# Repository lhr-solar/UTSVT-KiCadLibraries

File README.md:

# Common Libraries
This repository contains the footprint and symbol libraries that are used among us, the Longhorn Racing Solar Vehicles Team. 
In order to work on the hardware for our system, please follow the below standard practices when designing a new board.

# Using this Repository
In order to use the files in this repository, you must:
1. Add this repository as a submodule to the PCB repository. It will then show up as a folder within the PCB repository.
2. Create the PCB KiCAD Project and open it in KiCAD.
3. Click on `Preferences` -> `Manage Symbol Libraries` -> `Project Specific Libraries` and add the `.lib` files (within the submodule directory) to the path.
    
    **NOTE**: Ensure all `.lib` files are named `utsvt-name`

# Board Repositories
* All board repositories should contain this repository as a submodule.
* All board repositories should be named Team-BoardName (ex. BPS-LeaderPCB) - all board names should end in PCB
* All board repositories should have zip file of gerbers for the board
* All board repositories should contain pdf with images of board schematic and board layout (with dimensions)
* All board repositories should have `BoardName-backups/*` directory in their `.gitignore` file to ignore all backups generated.
* All board repositories should have README that contains the following information
    * Boards Purpose
    * Mouser link BOM for Board
    * List of components that take up vertical/horizontal volume outside of regular board dimensions (for mechanical purposes)
    * List of LED's on board and what information they provide

# Pull Request Template
The file PULL_REQUEST_TEMPLATE.md should be copied into the main board repository directory. This file creates a checklist of 
things the hardware engineer must complete after opening a PR. After submitting a PR, you must ensure this checklist is completed. Only after
the checklist is completed will a reviewer review your board.

    **NOTE**: After making changes to your board, it is essential that you re-request a review from the reviewers. Otherwise they will not know when
to review your design again. YOU MUST BE PROACTIVE IN YOUR WORK!

When first creating your board repository, and every time the Pull Request Template is updated, you must run the following command
`cp common/PULL_REQUEST_TEMPLATE.md .` to copy the Pull Request Template into the board repository.

# Adding Components to library
1. Add component information to Standardized Mouser Components Excel Sheet (this is so other designs can take this component into consideration if the use is applicable).
    * Be sure to include component name, mouser cart link, and footprint.
2. Open the PCB that you are working on in KiCAD (under its repository)
3. Click on `Symbol Editor`, select a `UTSVT` library to add it to, and click on `Add a New Symbol`.
4. Download component symbol and footprint (or make one yourself using symbol/footprint editor in KiCAD)
    * You may not need to download footprints/symbols for some components. Some footprints/symbols will work for multiple components if they are same package/pinout.
5. If component is large (vertically or horizontally), download 3d model for component.
6. All symbols should have the following information filled out when added:
    * Name
    * Datasheet/Mouser link
    * Footprint Association
7. If adding footprint, click on `Footprint Editor`, select a `UTSVT` folder to add it to.
8. If component takes up vertical or horizontal space (buck converters, connectors, large capacitors, etc.), follow the below steps:
    1. Download footprint and store in the submodule through your PCB repository
    2. Open KiCAD through your project file in your PCB repository. Select `Preferences` -> `Configure File Paths` -> `+` -> and add the following path `$(KIPRJMOD)/common/utsvt3d/`.
    3. Now when adding the 3D Model to the footprint, just select the footprint through the footprint library, click on 3D Models, and add the name of the step file (through one of the folders in `utsvt3d`).
9. After filling out the above information, enter the submodule directory through your PCB repository.
10. There will be changes made to this submodule if everything was done correctly. Now you must commit your changes to a new branch and open a Pull Request.
11. After the Pull Request is merged, update the submodule in your PCB repository through `git submodule update`.

# Standard Constraints for Laying out Board
When manufacturing a PCB, there are constraints that are given to us by the manufacturer based on how precise their manufacturing equipment is. The following are [**JLCPCB Manufacturing Capabilities**](https://jlcpcb.com/capabilities/Capabilities).  
When creating the layout of your board, select
`File` -> `Board Setup` -> `Constraints` and set them to the following values:
* Minimum Clearance (2 layer): .127mm
* Minimum Track Width (2 layer): .127mm
* Minimum Clearance (4 layer): .09mm
* Minimum Track Width (4 layer): .09mm
* Minimum Connection Width: 0mm
* Minimum Annular Width: .13mm
* Minimum Via Diameter (2 layer): .5mm
* Minimum Via Diameter (4 layer): .25mm
* Copper to Hole Clearance: .254mm
* Copper to Edge Clearance: .3mm
* Minimum Through Hole: .3mm
* Hole to Hole Clearance: .5mm
* Minimum Item Clearance: .15mm
* Minimum Text Height: 1mm
* Minimum Text Thickness: .153mm  

Also go `File` -> `Board Setup` -> `Solder Mask/Paste` and set them to the following values:
* Solder mask expansion: .038mm
* Solder mask minimum web width: .1mm  

# Exporting a Board as a 3D Model
Before exporting a board go into the 3D viewer of KiCAD `View` -> `3D Viewer` while in the PCB editor to see what you will be exporting. 
* For mechanical integration, mechanical doesn't need to see every individual component.  If your board doesn't have any smd parts that take up vertical or horizontal space then while in the 3D viewer do `Preferences` -> `Toggle SMD 3D Models` the same applies for any tht component except it's `Preferences` -> `Toggle Through Hole 3D Models`.  
* Go to `File` -> `Export` -> `Step` and select the directory you want to export to and in the `Coordinantes` section make sure `Board Center Origin` is selected.
* Press `Export`.

# Working on a Board
* The first page of the KiCAD schematic should have a version control description of the board that is being worked on. It should list the changes between each version of the board and changes that should be made in future versions of the board.
* When working on a board, the branch name should be the version of the board.
* Versions are updated every time the layout of the board is changed after a fabrication.
* Everyone working on boards should download the Interactive HTML BOM plugin for KiCAD. After laying out the board, an interactive BOM should be generated so soldering the board is easily managed.

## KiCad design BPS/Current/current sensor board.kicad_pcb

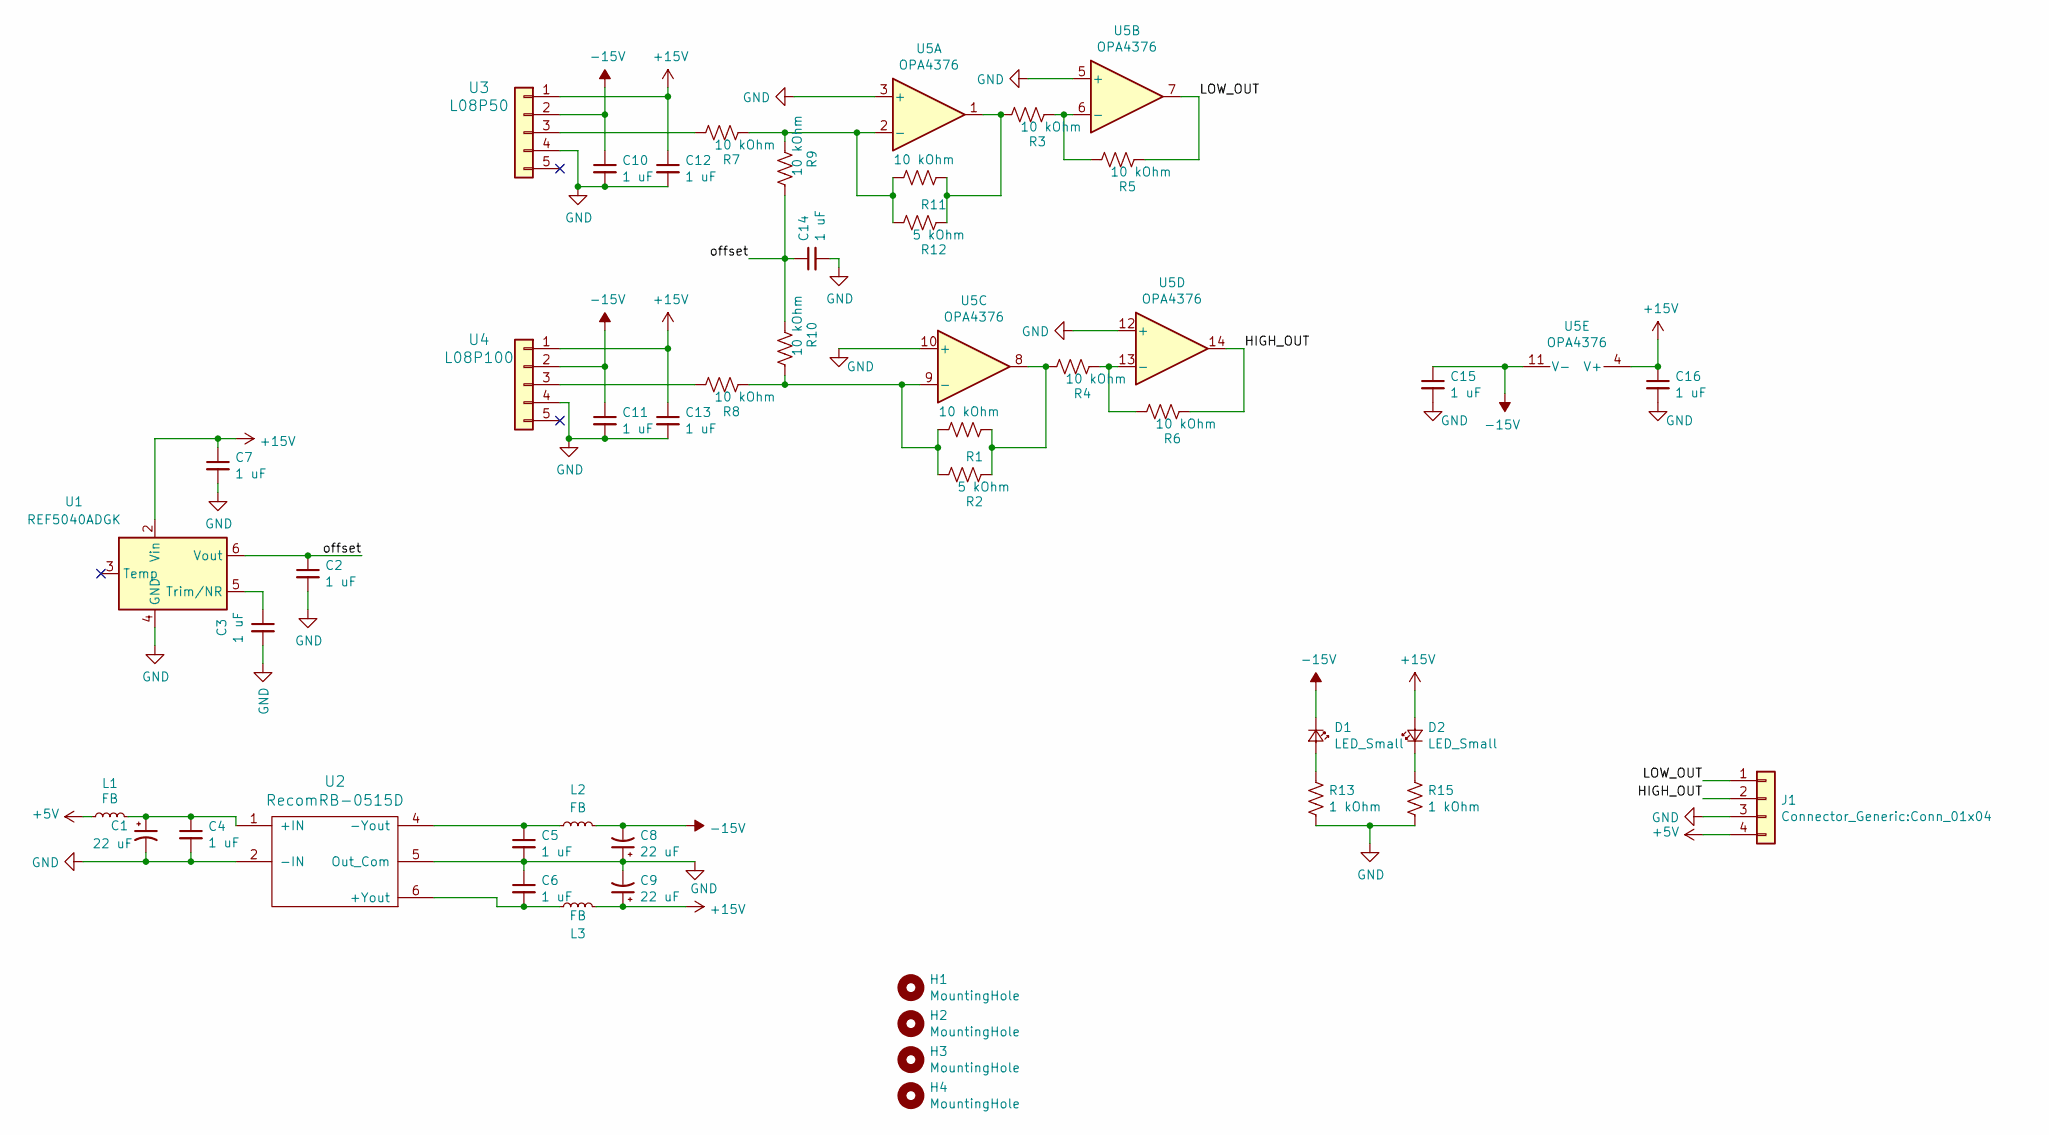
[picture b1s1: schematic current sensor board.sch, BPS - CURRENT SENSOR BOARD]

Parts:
C1, C8, C9: 22 uF; C_0805_2012Metric
C2, C3, C4, C5, C6, C7, C10, C11, C12, C13, C14, C15, C16: 1 uF; C_0805_2012Metric
D1, D2: LED_Small; LED_0805_2012Metric
H1, H2, H3, H4: MountingHole; MountingHole_3mm
J1: Connector_Generic:Conn_01x04; Molex_Micro-Fit_3.0_43650-0415_1x04_P3.00mm_Vertical
L1, L2, L3: FB; L_1206_3216Metric
R1, R3, R4, R5, R6, R7, R8, R9, R10, R11: 10 kOhm; R_0805_2012Metric
R2, R12: 5 kOhm; R_0805_2012Metric
R13, R15: 1 kOhm; R_0805_2012Metric
U1: REF5040ADGK; MSOP-8_3x3mm_P0.65mm
U2: RecomRB-0515D; SIP-7_19.6x6mm_P2.54mm
U3: L08P50; L08PxxxD15
U4: L08P100; L08PxxxD15
U5: OPA4376; TSSOP-14_4.4x5mm_P0.65mm

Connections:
+5V: J1.4, L1.1
+15V: C7.1, C9.1, C12.1, C13.1, C16.1, D2.2 (A), L3.2, U1.2 (Vin), U3.1, U4.1, U5.4 (V+)
-15V: C8.2, C10.1, C11.1, C15.1, D1.1 (K), L2.2, U3.2, U4.2, U5.11 (V-)
/HIGH_OUT: J1.2, R6.1, U5.14
/LOW_OUT: J1.1, R5.1, U5.7
/offset: C2.1, C14.1, R9.2, R10.1, U1.6 (Vout)
GND: C1.2, C2.2, C3.2, C4.2, C5.2, C6.1, C7.2, C8.1, C9.2, C10.2, C11.2, C12.2, C13.2, C14.2, C15.2, C16.2, J1.3, R13.2, R15.2, U1.4 (GND), U2.2 (-IN), U2.5 (Out_Com), U3.4, U4.4, U5.3 (+), U5.5 (+), U5.10 (+), U5.12 (+)
unnamed: C1.1, C4.1, L1.2, U2.1 (+IN)
unnamed: C3.1, U1.5 (Trim/NR)
unnamed: C5.1, L2.1, U2.4 (-Yout)
unnamed: C6.2, L3.1, U2.6 (+Yout)
unnamed: D1.2 (A), R13.1
unnamed: D2.1 (K), R15.1
unnamed: R1.1, R2.1, R4.2, U5.8
unnamed: R1.2, R2.2, R8.1, R10.2, U5.9 (-)
unnamed: R3.1, R5.2, U5.6 (-)
unnamed: R4.1, R6.2, U5.13 (-)
unnamed: R7.2, U3.3
unnamed: R8.2, U4.3
unnamed: R3.2, R11.1, R12.1, U5.1
unnamed: R7.1, R9.1, R11.2, R12.2, U5.2 (-)

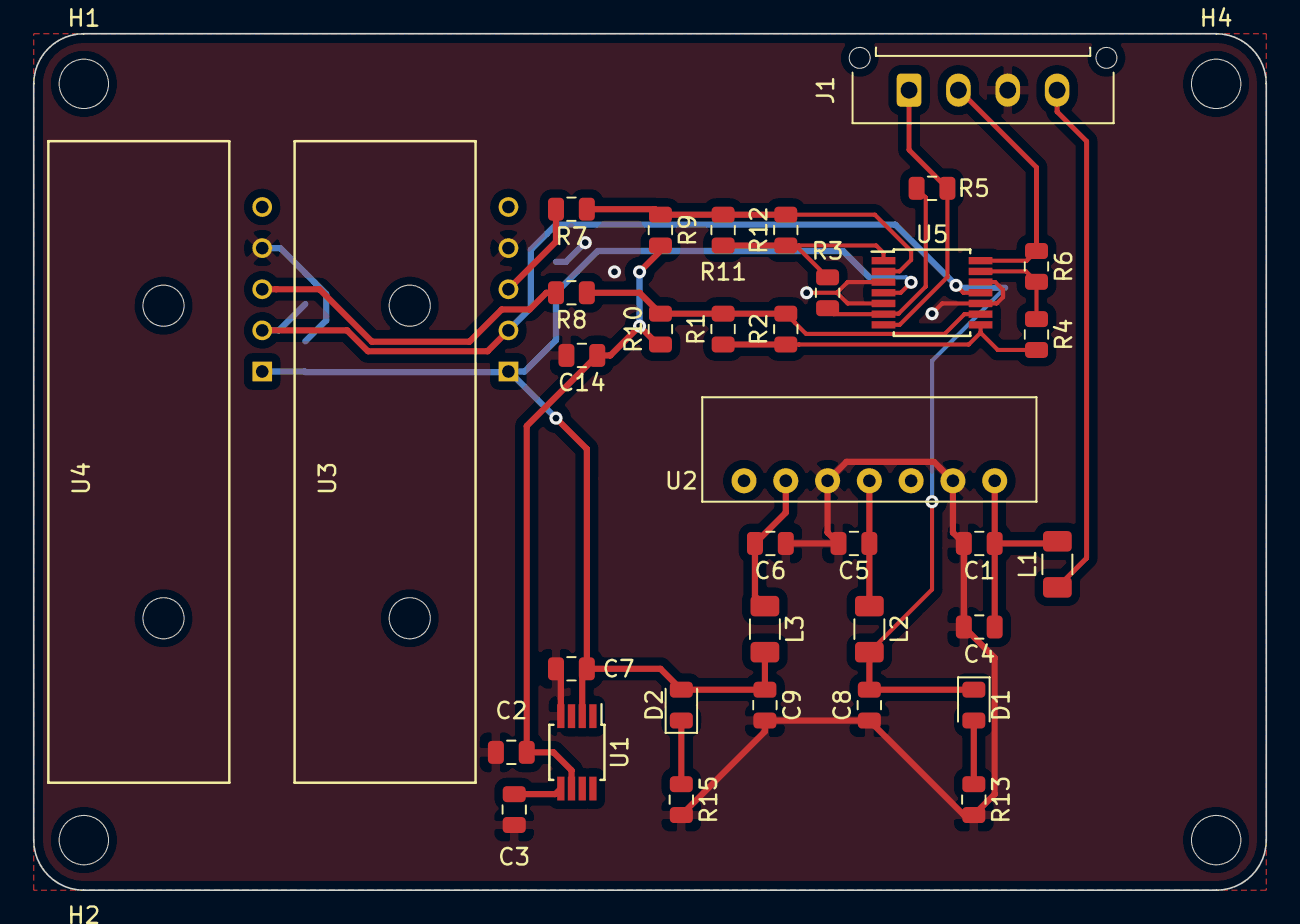
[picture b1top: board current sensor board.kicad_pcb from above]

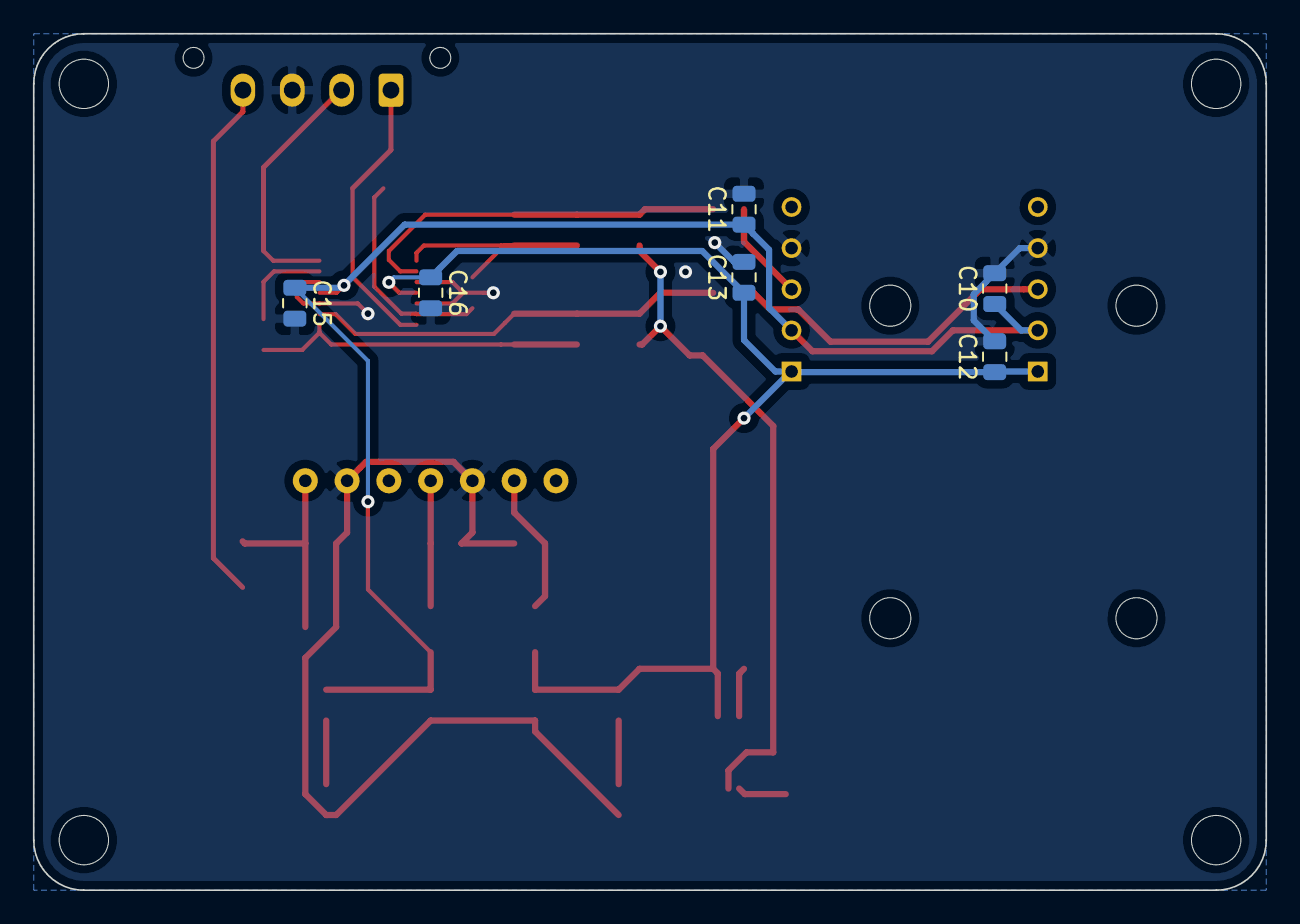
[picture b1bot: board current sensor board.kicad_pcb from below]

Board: 2 copper layers, 74.9 x 52.1 mm, 45 parts (6 on the bottom side), 21 nets.

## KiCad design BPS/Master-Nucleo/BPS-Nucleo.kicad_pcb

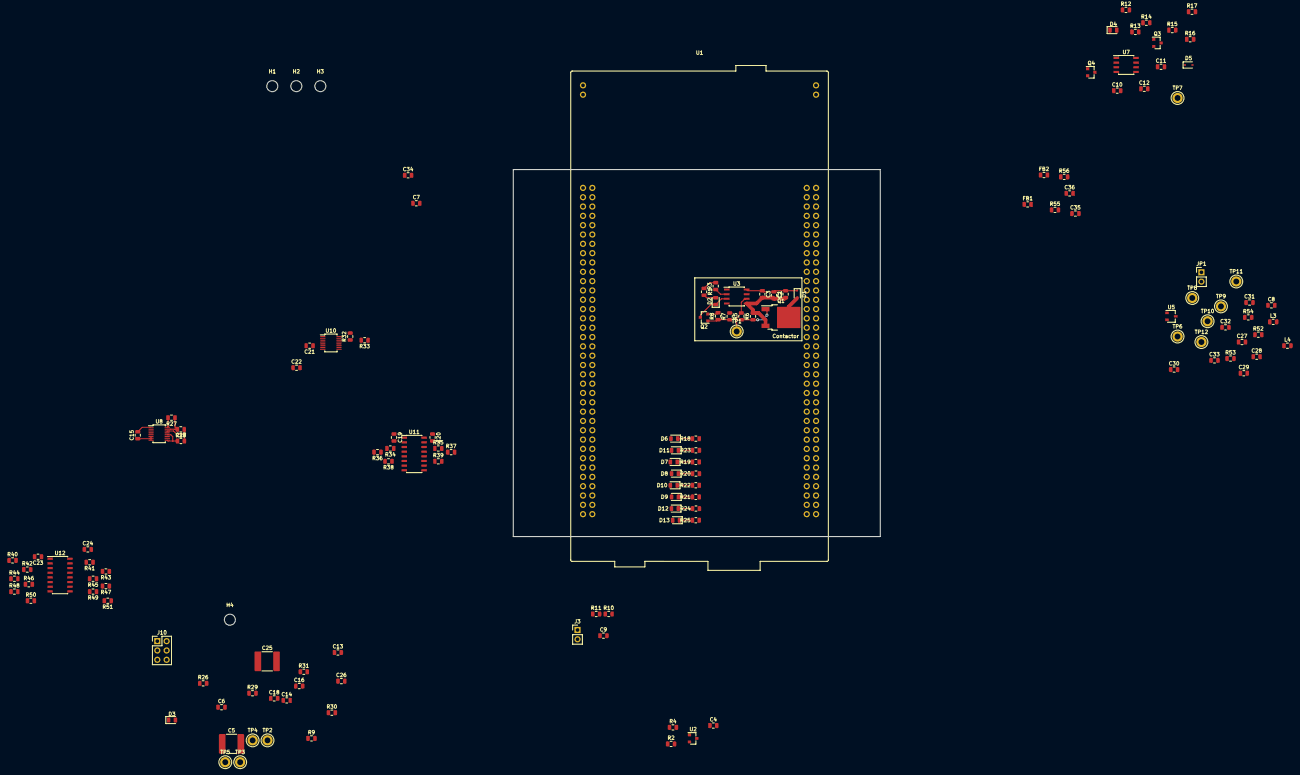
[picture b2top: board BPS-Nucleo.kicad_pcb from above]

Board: 2 copper layers, 100.0 x 100.0 mm, 141 parts (0 on the bottom side), 97 nets.

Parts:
C1, C4, C10: 1uF; C_0805_2012Metric
C2, C11, C27, C30: 10uF; C_0805_2012Metric
C3, C7, C9, C12, C15, C17, C19, C20, C21, C22, C23, C24, C28, C31, C32, C34: 0.1uF; C_0805_2012Metric
C5, C25: 470pF; C_2220_5650Metric
C6, C26: 4.7uF; C_0805_2012Metric
C8: 0.22uF; C_0805_2012Metric
C13, C14, C16, C18, C29, C33: 0.01uF; C_0805_2012Metric
C35, C36: 1u; C_0805_2012Metric
D1, D5: 1N4148WS; D_SOD-323
D2: ContactorEn; LED_0805_2012Metric
D3: PowerOn; LED_0805_2012Metric
D4: Fault; LED_0805_2012Metric
D6: Heartbeat; LED_0805_2012Metric
D7: UVolt; LED_0805_2012Metric
D8: OVolt; LED_0805_2012Metric
D9: OTemp; LED_0805_2012Metric
D10: OCurr; LED_0805_2012Metric
D11: WDError; LED_0805_2012Metric
D12: CANError; LED_0805_2012Metric
D13: Extra; LED_0805_2012Metric
FB1, FB2: 600; L_0805_2012Metric
H1, H2, H3, H4: MountingHole; MountingHole_3mm
J3: Conn_01x03; PinHeader_1x02_P2.54mm_Vertical
J10: DisplayJumper; PinHeader_2x03_P2.54mm_Vertical
JP1: Termination Resistors; PinHeader_1x02_P2.54mm_Vertical
L3, L4: 2kH; L_0805_2012Metric
Q1: VND5N07-E; TO-252-2
Q2, Q3, Q4: NTR4003NT1G; SOT-23
R1, R9: 1.5k; R_0805_2012Metric
R2, R10, R11: 4.7k; R_0805_2012Metric
R3, R12: 470; R_0805_2012Metric
R4: 1k; R_0805_2012Metric
R5, R7, R14, R16, R54: 0; R_0805_2012Metric
R6, R8, R15, R17: 10k; R_0805_2012Metric
R13: 1.6k; R_0805_2012Metric
R18: 680; R_0805_2012Metric
R19, R20, R21, R22, R23, R24, R25: 750; R_0805_2012Metric
R26: 120; R_0805_2012Metric
R27, R32: 806; R_0805_2012Metric
R28, R33: 1.21k; R_0805_2012Metric
R29, R30, R31: 49.9; R_0805_2012Metric
R34, R35, R36, R37, R38, R39, R40, R41, R42, R43, R44, R45, R46, R47, R48, R49, R50, R51: 50; R_0805_2012Metric
R52, R53: 60; R_0805_2012Metric
R55, R56: 220k; R_0805_2012Metric
TP1: ContactorGate_TP; TestPoint_Keystone_5005-5009_Compact
TP2: +12V_TP; TestPoint_Keystone_5005-5009_Compact
TP3: +5V_TP; TestPoint_Keystone_5005-5009_Compact
TP4: GNDPWR_TP; TestPoint_Keystone_5005-5009_Compact
TP5: GND_TP; TestPoint_Keystone_5005-5009_Compact
TP6: CAN_ISO_Vout; TestPoint_Keystone_5005-5009_Compact
TP7: StrobeLightGate_TP; TestPoint_Keystone_5005-5009_Compact
TP8: CAN_ISO_Vin; TestPoint_Keystone_5005-5009_Compact
TP9: CAN_ISO_GndIn; TestPoint_Keystone_5005-5009_Compact
TP10: CAN_ISO_GndOut; TestPoint_Keystone_5005-5009_Compact
TP11: CAN_H; TestPoint_Keystone_5005-5009_Compact
TP12: CAN_L; TestPoint_Keystone_5005-5009_Compact
U1: NUCLEO144-F412ZG; ST_Morpho_Connector_144_STLink
U2: BAS70-04; SOT-23
U3, U7: SI8261ABC-IS; SOIC-8_3.9x4.9mm_P1.27mm
U5: CDSOT23-T24CAN; SOT-23W
U8, U10: LTC6820; MSOP-16_3x4mm_P0.5mm
U11: Si8641EC-B-IS1; SOIC-16_3.9x9.9mm_P1.27mm
U12: SI8660EC-B-IS1; SOIC-16_3.9x9.9mm_P1.27mm

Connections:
+3V3: C7.2, C9.1, C21.1, C32.1, C33.1, J10.1, J10.2, R10.1, R11.1, U1.16, U10.6
+5V: C5.2, C15.1, C17.1, C19.1, C22.1, C23.1, C30.1, C31.1, C34.1, D4.2, R1.1, R2.2, R3.2, R9.1, R12.2, TP3.1, U1.6, U2.2, U8.6, U8.7, U8.8, U8.9, U8.12, U10.9, U10.12, U11.1, U11.7, U12.1
+5VL: C20.1, C24.1, C25.2, U11.10, U11.16, U12.16
+12V: C1.2, C2.1, C3.1, C6.1, C10.2, C11.1, C12.1, C26.1, D1.1, D5.1, TP2.1, U3.8, U7.8
/ADC1_CH2: C36.2, R56.2, U1.107
/ADC1_CH3: C35.2, R55.2, U1.109
/CAN/CAN_H: R52.2, TP11.1, U5.1
/CAN/CAN_L: R53.2, TP12.1, U5.2
/CAN/TERM_H: JP1.2, R52.1
/CAN/TERM_L: JP1.1, R53.1
/Contactor Driver/CONTACTOR_V-: D1.2, Q1.2
/DISPLAY_CS: U1.21, U10.5
/FAULT: R16.2, U1.88
/I2C3_SCL: J3.1, R10.2, U1.95
/I2C3_SDA: J3.2, R11.2, U1.73
/LTC6811_CS: U1.89, U8.5
/PA5: D13.2, U1.83
/PA6: D12.2, U1.85
/PA7: D11.2, U1.87
/PB0: R7.2, U1.34
/PB1: C4.1, R4.1, U1.96, U2.3
/PC0: D10.2, U1.38
/PC1: D9.2, U1.36
/PC2: D8.2, U1.35
/PC3: D7.2, U1.37
/RUN: D6.2, U1.28
/SPI1_CLK: R34.2, U1.103, U8.4, U10.4
/SPI1_MISO: R38.2, U1.99, U8.3, U10.3
/SPI1_MOSI: R36.2, U1.101, U8.2, U10.2
/SPI/DISP_IM: R31.1, U10.10
/SPI/DISP_IP: R30.1, U10.11
/SPI/DISP_PHA: J10.4, U10.8
/SPI/DISP_POL: J10.3, U10.7
/SPI/VOLT_IM: R26.1, R29.1, U8.10
/SPI/VOLT_IP: R26.2, U8.11
/TEMP_CS1: R40.1, U1.102
/TEMP_CS2: R42.1, U1.100
/TEMP_CS3: R44.1, U1.98
/TEMP_CS4: R46.1, U1.76
/TEMP_CS5: R48.1, U1.91
/TEMP_CS6: R50.1, U1.74
GND: C4.2, C7.1, C9.2, C13.2, C14.2, C15.2, C16.2, C17.2, C18.2, C19.2, C21.2, C22.2, C23.2, C30.2, C31.2, C32.2, C33.2, C34.2, C35.1, C36.1, D3.1, J10.5, J10.6, Q2.2, Q4.2, R8.2, R17.2, R18.2, R19.2, R20.2, R21.2, R22.2, R23.2, R24.2, R25.2, R28.1, R33.1, TP5.1, U1.8, U1.19, U1.20, U1.22, U1.49, U1.60, U1.71, U1.72, U1.81, U1.92, U1.104, U1.111, U1.126, U1.135, U1.143, U1.144, U2.1, U8.1, U8.13, U8.14, U10.1, U10.13, U10.14, U11.2, U11.8, U12.8
GNDPWR: C1.1, C2.2, C3.2, C6.2, C10.1, C11.2, C12.2, C26.2, Q1.3, Q3.2, R6.2, R15.2, TP4.1, U3.5, U7.5
GND_A: C20.2, C24.2, U11.9, U11.15, U12.9
unnamed: C8.1, L3.2, TP6.1
unnamed: C8.2, L4.2, TP10.1
unnamed: C14.1, R29.2
unnamed: C18.1, R30.2, R31.2
unnamed: C27.1, C28.1, C29.1, L3.1, TP8.1
unnamed: C27.2, C28.2, C29.2, L4.1, R54.2, TP9.1, U5.3
unnamed: D2.1, Q2.3, U3.3
unnamed: D2.2, R1.2
unnamed: D3.2, R9.2
unnamed: D4.1, R13.1
unnamed: D5.2, Q3.3
unnamed: D6.1, R18.1
unnamed: D7.1, R19.1
unnamed: D8.1, R20.1
unnamed: D9.1, R21.1
unnamed: D10.1, R22.1
unnamed: D11.1, R23.1
unnamed: D12.1, R24.1
unnamed: D13.1, R25.1
unnamed: FB1.2, R55.1
unnamed: FB2.2, R56.1
unnamed: R2.1, R4.2
unnamed: Q1.1, R5.1, R6.1
unnamed: Q2.1, R7.1, R8.1
unnamed: Q3.1, R14.1, R15.1
unnamed: Q4.1, R16.1, R17.1
unnamed: Q4.3, R13.2, U7.3
unnamed: R3.1, U3.2
unnamed: R5.2, TP1.1, U3.6
unnamed: R12.1, U7.2
unnamed: R14.2, TP7.1, U7.6
unnamed: R27.1, R28.2, U8.15
unnamed: R27.2, U8.16
unnamed: R32.1, R33.2, U10.15
unnamed: R32.2, U10.16
unnamed: R34.1, U11.3
unnamed: R35.1, U11.14
unnamed: R36.1, U11.4
unnamed: R37.1, U11.13
unnamed: R38.1, U11.6
unnamed: R39.1, U11.11
unnamed: R40.2, U12.2
unnamed: R41.2, U12.15
unnamed: R42.2, U12.3
unnamed: R43.2, U12.14
unnamed: R44.2, U12.4
unnamed: R45.2, U12.13
unnamed: R46.2, U12.5
unnamed: R47.2, U12.12
unnamed: R48.2, U12.6
unnamed: R49.2, U12.11
unnamed: R50.2, U12.7
unnamed: R51.2, U12.10

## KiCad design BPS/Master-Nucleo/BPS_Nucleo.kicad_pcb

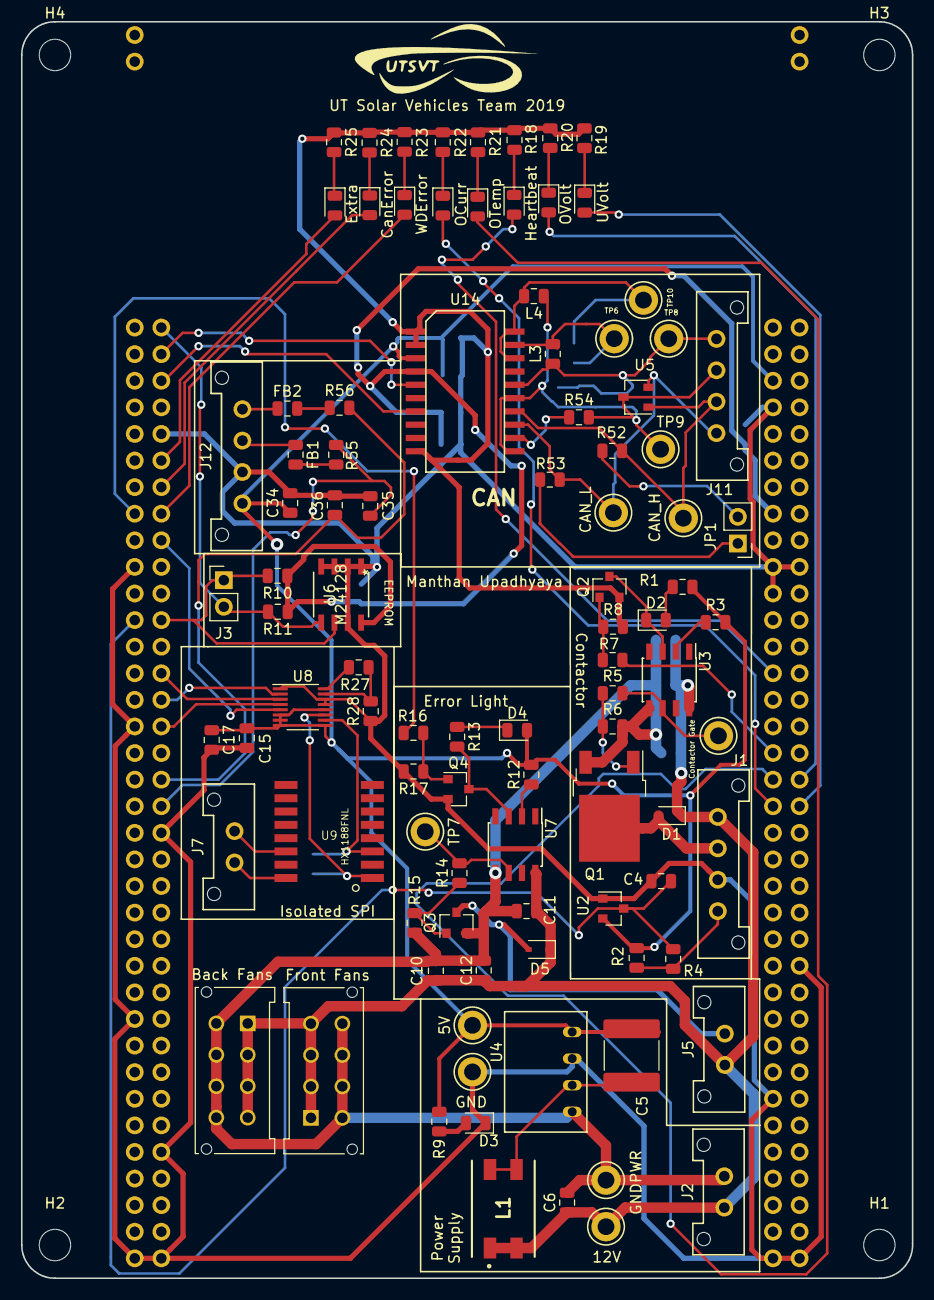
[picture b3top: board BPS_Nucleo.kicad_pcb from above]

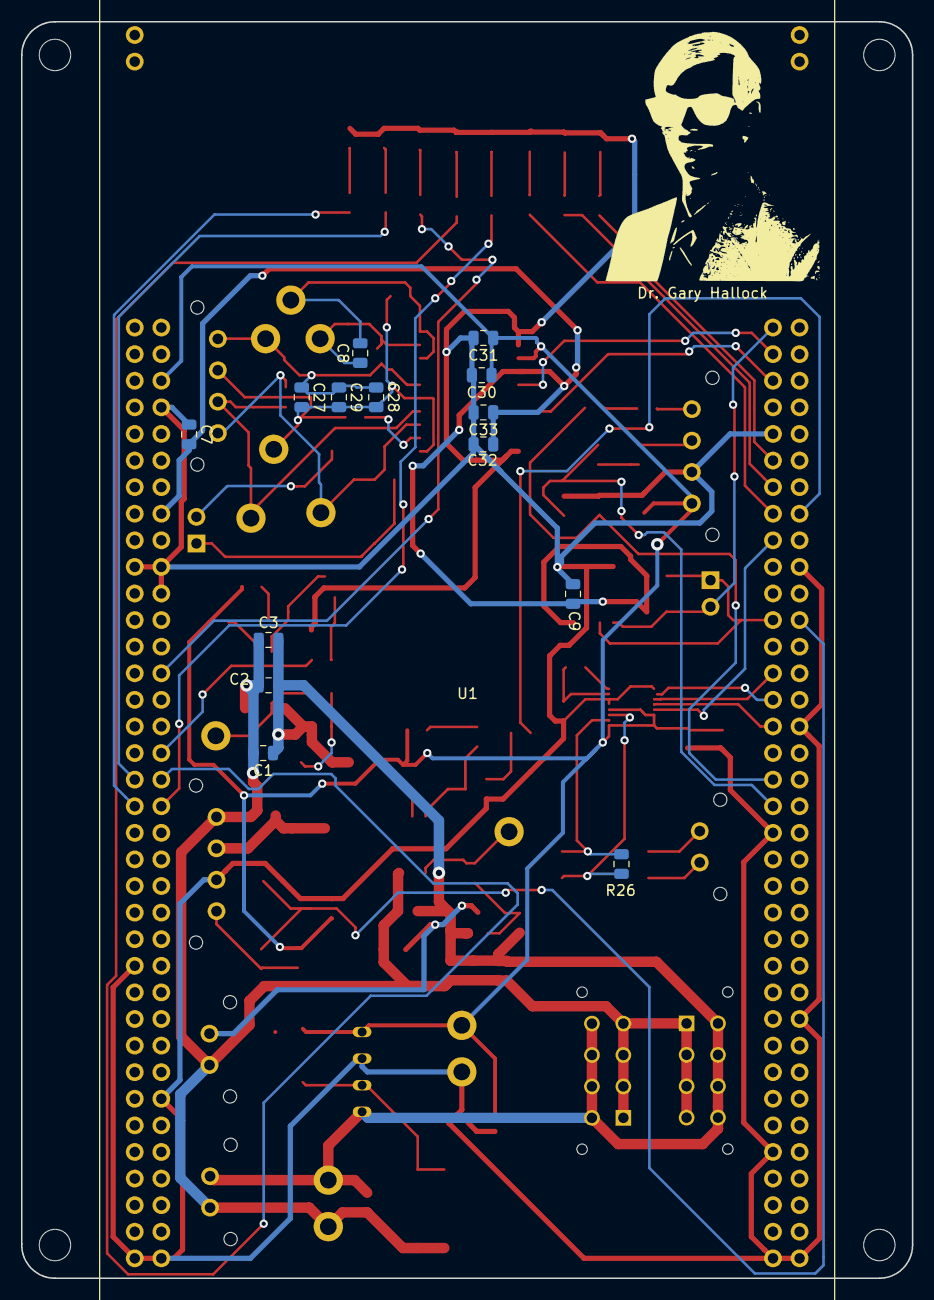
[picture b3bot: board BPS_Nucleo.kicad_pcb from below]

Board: 2 copper layers, 85.1 x 120.0 mm, 115 parts (15 on the bottom side), 70 nets.

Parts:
5V: +5V_TP; TestPoint_Keystone_5005-5009_Compact
12V: +12V_TP; TestPoint_Keystone_5005-5009_Compact
Back Fans: BackFans; Molex_MicroFit3.0_2x4xP3.00mm_PolarizingPeg_Vertical
C1, C4, C10: 1uF; C_0805_2012Metric
C2, C11, C27, C30: 10uF; C_0805_2012Metric
C3, C7, C9, C12, C15, C17, C28, C31, C32, C34: 0.1uF; C_0805_2012Metric
C5: 470pF; C_2220_5650Metric
C6: 4.7uF; C_0805_2012Metric
C8: 0.22uF; C_0805_2012Metric
C29, C33: 0.01uF; C_0805_2012Metric
C35, C36: 1u; C_0805_2012Metric
CAN_H: CAN_H; TestPoint_Keystone_5005-5009_Compact
CAN_L: CAN_L; TestPoint_Keystone_5005-5009_Compact
CanError: CANError; LED_0805_2012Metric
Contactor Gate: ContactorGate_TP; TestPoint_Keystone_5005-5009_Compact
D1, D5: 1N4148WS; D_SOD-323
D2: ContactorEn; LED_0805_2012Metric
D3: PowerOn; LED_0805_2012Metric
D4: Fault; LED_0805_2012Metric
Extra: Extra; LED_0805_2012Metric
FB1, FB2: 600; L_0805_2012Metric
Front Fans: FrontFans; Molex_MicroFit3.0_2x4xP3.00mm_PolarizingPeg_Vertical
GND: GND_TP; TestPoint_Keystone_5005-5009_Compact
GNDPWR: GNDPWR_TP; TestPoint_Keystone_5005-5009_Compact
H1, H2, H3, H4: MountingHole; MountingHole_3mm
Heartbeat: Heartbeat; LED_0805_2012Metric
J1: ContactorConnector; Molex_MicroFit3.0_1x4xP3.00mm_PolarizingPeg_Vertical
J2: CarPowerConnector; Molex_MicroFit3.0_1x2xP3.00mm_PolarizingPeg_Vertical
J3: Conn_01x03; PinHeader_1x02_P2.54mm_Vertical
J5: ErrorLightConnector; Molex_MicroFit3.0_1x2xP3.00mm_PolarizingPeg_Vertical
J7: VoltageSlaveConnector; Molex_MicroFit3.0_1x2xP3.00mm_PolarizingPeg_Vertical
J11: CAN_Out; Molex_MicroFit3.0_1x4xP3.00mm_PolarizingPeg_Vertical
J12: Conn_01x04; Molex_MicroFit3.0_1x4xP3.00mm_PolarizingPeg_Vertical
JP1: Termination Resistors; PinHeader_1x02_P2.54mm_Vertical
L1: 10uH; SRF0905A
L3, L4: 2kH; L_0805_2012Metric
OCurr: OCurr; LED_0805_2012Metric
OTemp: OTemp; LED_0805_2012Metric
OVolt: OVolt; LED_0805_2012Metric
Q1: VND5N07-E; TO-252-2
Q2, Q3, Q4: NTR4003NT1G; SOT-23
R1, R9: 1.5k; R_0805_2012Metric
R2, R10, R11: 4.7k; R_0805_2012Metric
R3, R12: 470; R_0805_2012Metric
R4: 1k; R_0805_2012Metric
R5, R7, R14, R16, R54: 0; R_0805_2012Metric
R6, R8, R15, R17: 10k; R_0805_2012Metric
R13: 1.6k; R_0805_2012Metric
R18: 680; R_0805_2012Metric
R19, R20, R21, R22, R23, R24, R25: 750; R_0805_2012Metric
R26: 120; R_0805_2012Metric
R27: 806; R_0805_2012Metric
R28: 1.21k; R_0805_2012Metric
R52, R53: 60; R_0805_2012Metric
R55, R56: 220k; R_0805_2012Metric
TP6: CAN_ISO_Vout; TestPoint_Keystone_5005-5009_Compact
TP7: StrobeLightGate_TP; TestPoint_Keystone_5005-5009_Compact
TP8: CAN_ISO_Vin; TestPoint_Keystone_5005-5009_Compact
TP9: CAN_ISO_GndIn; TestPoint_Keystone_5005-5009_Compact
TP10: CAN_ISO_GndOut; TestPoint_Keystone_5005-5009_Compact
U1: NUCLEO144-F412ZG; ST_Morpho_Connector_144_STLink
U2: BAS70-04; SOT-23
U3, U7: SI8261ABC-IS; SOIC-8_3.9x4.9mm_P1.27mm
U4: RI3-1205S; RI3_DC_Converter
U5: CDSOT23-T24CAN; SOT-23W
U6: M24128; M24128-BRMN6P
U8: LTC6820; MSOP-16_3x4mm_P0.5mm
U9: HX1188FNL; HXXXX
U14: ADM3055E; SOIC-20W_7.5x15.4mm_Pitch1.27mm
UVolt: UVolt; LED_0805_2012Metric
WDError: WDError; LED_0805_2012Metric

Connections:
+3V3: C7.2, C9.1, C32.1, C33.1, R10.1, R11.1, U1.16, U6.8, U14.4
+5V: 5V.1, C5.2, C15.1, C17.1, C30.1, C31.1, C34.1, D4.2, J12.1, R1.1, R2.2, R3.2, R9.1, R12.2, U1.6, U2.2, U4.4, U8.6, U8.7, U8.8, U8.9, U8.12, U14.3
+12V: 12V.1, Back Fans.1, Back Fans.2, Back Fans.3, Back Fans.4, C1.2, C2.1, C3.1, C6.1, C10.2, C11.1, C12.1, D1.1, D5.1, Front Fans.1, Front Fans.2, Front Fans.3, Front Fans.4, J1.1, J2.1, J5.1, L1.1, L1.2, U3.8, U7.8
/ADC1_CH2: C36.2, R56.2, U1.107
/ADC1_CH3: C35.2, R55.2, U1.109
/CAN1_RX: U1.75, U14.5
/CAN1_TX: U1.77, U14.7
/CAN/CAN_H: CAN_H.1, J11.3, R52.2, U5.1, U14.14
/CAN/CAN_L: CAN_L.1, J11.4, R53.2, U5.2, U14.13
/CAN/RSlope: R54.1, U14.12
/CAN/TERM_H: JP1.2, R52.1
/CAN/TERM_L: JP1.1, R53.1
/Contactor Driver/CONTACTOR_V-: D1.2, J1.2, Q1.2
/FAULT: R16.2, U1.88
/I2C3_SCL: J3.1, R10.2, U1.95, U6.6
/I2C3_SDA: J3.2, R11.2, U1.73, U6.5
/LTC6811_CS: U1.89, U8.5
/PA5: Extra.2, U1.83
/PA6: CanError.2, U1.85
/PA7: U1.87, WDError.2
/PB0: R7.2, U1.34
/PB1: C4.1, R4.1, U1.96, U2.3
/PC0: OCurr.2, U1.38
/PC1: OTemp.2, U1.36
/PC2: OVolt.2, U1.35
/PC3: U1.37, UVolt.2
/RUN: Heartbeat.2, U1.28
/SPI1_CLK: U1.103, U8.4
/SPI1_MISO: U1.99, U8.3
/SPI1_MOSI: U1.101, U8.2
/SPI/VOLT_IM: R26.1, U8.10, U9.3
/SPI/VOLT_IP: R26.2, U8.11, U9.1
GND: C4.2, C7.1, C9.2, C15.2, C17.2, C30.2, C31.2, C32.2, C33.2, C34.2, C35.1, C36.1, D3.1, GND.1, J1.3, J12.2, Q2.2, Q4.2, R8.2, R17.2, R18.2, R19.2, R20.2, R21.2, R22.2, R23.2, R24.2, R25.2, R28.1, U1.8, U1.19, U1.20, U1.22, U1.49, U1.60, U1.71, U1.72, U1.81, U1.92, U1.104, U1.111, U1.126, U1.135, U1.143, U1.144, U2.1, U4.3, U6.1, U6.2, U6.3, U6.4, U6.7, U8.1, U8.13, U8.14, U14.1, U14.2, U14.10
GNDPWR: Back Fans.5, Back Fans.6, Back Fans.7, Back Fans.8, C1.1, C2.2, C3.2, C6.2, C10.1, C11.2, C12.2, Front Fans.5, Front Fans.6, Front Fans.7, Front Fans.8, GNDPWR.1, J2.2, Q1.3, Q3.2, R6.2, R15.2, U3.5, U4.1, U7.5
unnamed: C5.1, L1.3, L1.4, U4.2
unnamed: C8.1, L3.2, TP6.1, U14.19
unnamed: C8.2, L4.2, TP10.1, U14.18, U14.20
unnamed: C27.1, C28.1, C29.1, J11.1, L3.1, TP8.1, U14.16
unnamed: C27.2, C28.2, C29.2, J11.2, L4.1, R54.2, TP9.1, U5.3, U14.11, U14.15
unnamed: D2.1, Q2.3, U3.3
unnamed: D2.2, R1.2
unnamed: D3.2, R9.2
unnamed: D4.1, R13.1
unnamed: D5.2, J5.2, Q3.3
unnamed: Heartbeat.1, R18.1
unnamed: R19.1, UVolt.1
unnamed: OVolt.1, R20.1
unnamed: OTemp.1, R21.1
unnamed: OCurr.1, R22.1
unnamed: R23.1, WDError.1
unnamed: CanError.1, R24.1
unnamed: Extra.1, R25.1
unnamed: FB1.1, J12.3
unnamed: FB1.2, R55.1
unnamed: FB2.1, J12.4
unnamed: FB2.2, R56.1
unnamed: J1.4, R2.1, R4.2
unnamed: J7.1, U9.16
unnamed: J7.2, U9.14
unnamed: Q1.1, R5.1, R6.1
unnamed: Q2.1, R7.1, R8.1
unnamed: Q3.1, R14.1, R15.1
unnamed: Q4.1, R16.1, R17.1
unnamed: Q4.3, R13.2, U7.3
unnamed: R3.1, U3.2
unnamed: Contactor Gate.1, R5.2, U3.6
unnamed: R12.1, U7.2
unnamed: R14.2, TP7.1, U7.6
unnamed: R27.1, R28.2, U8.15
unnamed: R27.2, U8.16

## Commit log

2019-10-12 Refactor current folders and remake current board
2019-10-12 Add a pdf of the schematic
2019-11-08 Connected all PCB components. Space in middle cannot be utilized. Distance between traces and copper must be less than .127mm or 5 mils according to manufacturer capabilities.
2019-11-09 Before, the components were divided between left and right. Now, they are between the top and right and all connectors are towards the edge.
2019-11-09 Fixed a few connections I didn't notice earlier.
2019-11-16 Move connector and round corners, generate gerbers
2019-11-16 Before, components were outside board. Moved components to inside of board so usb port is unobstructed. Distance between copper and traces should be 5 mils.
2019-11-16 Added silkscreens to certain diodes and testpoints
2019-11-17 Increased area of PCB to include upper components. Added silkscreen of Dr. Hallock.
2019-11-19 Decreased length of PCB on top, left, and bottom and spaced out some resistors in the EEPROM.
2019-11-23 Added mounting holes and footprints. Increased track length of 5v from .25 to .38.
2020-08-02 Set up the common libaries repository
2020-08-02 Extract the symbols from the common folder.
2020-08-06 Adds BAS70-04
2020-08-13 Updates BAS70-04 symbol
2020-09-01 Adds power footprint library
2020-09-01 Deletes useless file
2020-09-12 Adds footprints and symbols for the controls leader board
2020-09-19 Places HX1188FNL transformer into common library
2020-09-19 Adds ethernet transceiver
2020-09-19 Adds GPS MTK3339 to library
2020-09-19 Add GPS unit footprint
2020-10-03 Adds LTC6820 to utsvt-chips
2020-10-10 Add Molex 3D Models
2020-10-10 Assign 3D models to molex connectors
2020-10-10 Adjust paths
2020-10-24 Add more 3D models for connectors
2020-10-29 Add 3d models relevant to the telemetry board.
2020-12-05 Add more components for the battery secondary
2020-12-05 Add more components for the battery primary
2020-12-18 Adds power components and op amps for the supplemental monitoring board
2020-12-18 Banana jack connector
2020-12-20 Adds opamp and dc-dc converter for supplemental monitoring board
2021-01-06 Adds DC-DC converters from BPS Test Board
2021-01-23 Added HX1188FNL chip, 2222 5750 Metric capacitor (2.6mm in height), and 3 hole horizontal connector
2021-01-23 Adds RSD-150 and 2 pin molex connector
2021-01-23 adds 3D models
2021-01-25 added controls leader board models
2021-02-06 updated common with controls parts
2021-10-02 Some more chips
2021-11-06 New ADC
2021-12-24 Fix power regulators
2022-09-24 new footprint for Vishay shunt resistor and DPST switch
2022-09-24 fixed files
2022-09-24 Adds switch
2022-09-24 Adds new switch
2022-09-24 New SP3T Footprint
2022-10-01 Added new component footprints for BPS scrutineering board
2022-10-15 added switch
2022-10-22 switches
2023-01-21 add padp-24v connector footprint
2023-04-29 Added BPS components
2023-05-02 Adding documentation and standards
2023-05-04 Added more procedures
2023-05-04 Added more procedures for footprints
2023-05-05 Added Matthews comments
2023-05-05 Forgot to save file in vscode hehe
2023-05-05 Standardized constraints
2023-05-06 Updates symbols for Kicad 7
2023-05-07 More documentation changes
2023-05-16 Adding information to OPA21x symbol
2023-05-21 Added info on how to add 3D Models to repository
2023-05-22 Support for Controls Simboard
    Added 3D Models and updated footprints for parts used in Control Simboard
2023-05-22 lan chip 3d model
2023-05-22 3d model linking
2023-05-22 further footprint/model linking
2023-05-22 Updated 3dModel step to be project specific
2023-05-22 Removed unnecessary files
2023-05-22 Added BPS Minion Shield Connector
2023-05-22 move reference
2023-05-23 more models
2023-05-28 Added ref to footprint
2023-05-30 footprint margins and proper references
2023-05-30 remove schematic specific properties
2023-05-30 Ri3_DC_Converter courtyard
2023-05-31 Added datasheet, added connector silkscreen, and extended keepout layer
2023-06-08 Added 3D models
2023-06-11 Moved connector 3d model to utsvt3d
2023-06-14 Added 3d models and footprints for Controls Simboard PCB
2023-06-17 new bt breakout board
2023-06-19 Added rotary encoder 3d model
2023-07-04 add D5V0P4UR6SO-7
2023-07-14 Added SOM connector
2023-07-14 Cleaned up connector footprint
2023-07-14 Added connector 3D model
2023-07-16 new molex connector footprint
2023-07-18 added instructions on how to export boards as 3D models
2023-07-20 Added 3D models for connectors and chips
2023-07-26 Added new connectors
2023-07-28 Added 3x2 molex connector 3D model
2023-07-31 Added .DS_Store to gitignore
2023-08-08 Bps minion standardization (#14)
    * Added 3D models
    * Moved connector 3d model to utsvt3d
2023-08-08 Telemetry primary standardization (#13)
    * lan chip 3d model
    * 3d model linking
    * further footprint/model linking
    * more models
    * footprint margins and proper references
    * remove schematic specific properties
2023-08-09 Fixed Power Regulator Symbols/Footprints
2023-08-26 boot connector
2023-09-02 added SOMConnector symbol
2023-09-02 added SW pull up ic
2023-09-09 added file 151035-0002.stp in utsvt3d/connectors.3dshapes for Contactor-DriverPCB standardization
2023-09-12 unsus
2023-09-13 Peripheral som changes (#16)
    * add D5V0P4UR6SO-7
    * Added SOM connector
    * Cleaned up connector footprint
    * Added connector 3D model
    * new molex connector footprint
    * Added 3D models for connectors and chips
2023-09-21 Added new 3D model instructions
2023-09-21 Added new 3D model instructions (#17)
2023-09-21 Added BPS Minion Shield Connector (#12)
    * Added BPS Minion Shield Connector
    * move reference
    * Added ref to footprint
    * Added datasheet, added connector silkscreen, and extended keepout layer
    ---------
2023-09-23 Added BTB silkscreen footprint
2023-09-23 Add mux chip
2023-09-23 add footprint
2023-09-23 removed deprecated libraries
2023-09-29 stuff
2023-09-30 Added DaughterBoard Connector
2023-09-30 Added Fan Controller IC Symbol
2023-09-30 airflow symbols
2023-09-30 tempSensor
2023-09-30 fixed symbols
2023-09-30 path fixes
2023-09-30 Changed Daughter SOM Connector to have Daughter Connector
2023-09-30 adc symbol element
2023-09-30 Added 3D model for Daugter Connector
2023-09-30 xbee
2023-10-07 added new chip
2023-10-07 add isolator chip
2023-10-07 BMS Chip
2023-10-07 added 3d model for 3-pin vertical connector for temp sensors
2023-10-08 added peripheralsom footprint
2023-10-08 Added part number to PeripheralSOM_Connector
2023-10-08 Added 3D model of PeripheralSOM
2023-10-08 Peripheral som symbol (#19)
    * added peripheralsom footprint
    * Added part number to PeripheralSOM_Connector
    * Added 3D model of PeripheralSOM
2023-10-14 new voltage regulator chip
2023-10-14 mod bms chip
2023-10-21 new som changes
2023-10-28 Babu the Builder footprint added
2023-11-02 new chip
2023-11-04 Revert "new chip"
    This reverts commit 48b5eece43e9e1dbe76317947bf46eea84493602.
2023-11-04 add iso1640bdr isolator
2023-11-04 Banana Plug Horizontal Connector
2023-11-04 Battery Holder Footprints
2023-11-04 power fixes
2023-11-04 new power module
2023-11-05 Updated symbols
2023-11-05 7 segment
2023-11-05 oops
2023-11-06 asdf
2023-11-08 (￣y▽￣)╭ Ohohoho.....
2023-11-11 Male and Female connectors
2023-11-11 connector footprints (#21)
    * Banana Plug Horizontal Connector
    * Battery Holder Footprints
    * Male and Female connectors
2023-11-11 added LeaderSOM 3D files
2023-11-12 added proper LED display 3D model
2023-11-23 Added LeaderSOM 3D model
2023-12-02 Added GPIO extender chip
2023-12-02 Replaced GPIO ettender with a larger one
2023-12-02 Added footprint for GPIO expander chip
2023-12-18 cleanup duplicates
2023-12-18 update peripheral som symbol
2023-12-18 Added fan chip cuz Champers sucks
2023-12-18 Champers doesn't suck. Lakshay is silly
    This reverts commit 726b292cddfffd021cfc97640fa1f3c9100521ce.
2023-12-18 linked 3D models to footprints
2023-12-18 Lakshay isn't silly. Champers sucks
2023-12-23 made perhiperal symbol cuter :3
2023-12-23 added board and USB outline to peripheral footprint
2023-12-23 fixed datasheet on ADC and BMS chip
2023-12-29 Started adding instructions
2023-12-29 Added source link for manufacturing capabilities
2024-01-04 Started documentation script
2024-01-04 added STEP and PCB export
2024-01-04 better formatting
2024-01-04 Added comments
2024-01-04 Added script
2024-01-04 added to do
2024-01-04 fixed via diameter
2024-01-04 finished cons
2024-01-04 readme work now
2024-01-04 fixed readme 2
2024-01-04 SVG exports all layers and also output an outline STEP
2024-01-07 addressed changes
2024-01-07 UTSVT is dead and COMMONism lives
2024-01-07 .DS_Store reducted to atoms
2024-01-07 Jlc constraints updates (#25)
    * Started adding instructions
    * Added source link for manufacturing capabilities
    * fixed via diameter
    * finished cons
    * readme work now
    * fixed readme 2
2024-01-10 death to COMMONism
2024-01-12 weeeeeeeeeeeeeeeeeee (addded solder mask constraints)
2024-01-12 markdown is stupid
2024-01-14 fix adc footprint
2024-01-18 GPIO extender IC footprint
2024-03-19 added footprints and 3d models
2024-03-25 added footprints and 3d models for DC-DC Fuse PCB(#28)
2024-04-23 Added high current diode
2024-06-02 modified libraries for USBC Power PCB
2024-06-23 add TPS62933 buck converter
2024-07-27 Merge SOM components to master (#22)
    * Added DaughterBoard Connector
    * Added Fan Controller IC Symbol
    * Changed Daughter SOM Connector to have Daughter Connector
    * Added 3D model for Daugter Connector
    * added new chip
    * Updated symbols
2024-07-27 moving laptops
2024-08-14 new symbol for seven segment display and mcu
2024-08-14 changed 2-channel to 1-channel current sense INAx180
2024-08-15 Added many of the footprints for bucks & inductors
2024-08-21 added new bucks + USB chip
2024-08-22 added 3.3V iso buck
2024-08-22 add P/N field
2024-08-22 add DC-DC 3d model
2024-08-31 library updates
2024-08-31 removed stuff that i removed, added stuff i added
2024-09-01 add mosfet footprint and usb c connector footprint
2024-09-07 added current limit chip & more current on isolator
2024-09-07 checked out some footprints from master
2024-09-14 footprints and symbols
2024-09-15 gabagool
2024-09-19 banana
2024-09-23 added diff footprint for 5v inductor
2024-09-26 added troll & some 3d files
2024-09-27 Added new Power NMOS
2024-09-29 Added Contactor Flyback Schottky Diode Footprint
2024-09-29 Added Contactor Flyback Schottky Diode Footprint (#30)
2024-09-30 r u a fan of that??????????
2024-09-30 added new SOM connectr
2024-10-05 remove old SOM connector + add new one
2024-10-05 started psom symbol (no footprint)
2024-10-06 yipee
2024-10-07 added R13 3d model
2024-10-11 psom footprint
2024-10-11 changed edgecut to user.drawings
2024-10-11 moved stuff around
2024-10-11 fixed 3d model path
2024-10-12 remove old SOM symbols
2024-10-12 Psom symbol (#31)
    * started psom symbol (no footprint)
    * yipee
    * psom footprint
    * changed edgecut to user.drawings
    * moved stuff around
    * fixed 3d model path
2024-10-12 Revert "remove old SOM symbols"
    This reverts commit 250cbcc2e2dcc47e9e2776a6e016be1b7e71c158.
2024-10-12 added 16 channel adc/mux, revised psom symbol
2024-10-12 added 16 channel adc/mux, revised psom symbol (#33)
2024-10-12 Added standard pmos symbol
2024-10-12 Added standard pmos symbol (#34)
2024-10-17 symbol for Peripheral CAN connector
2024-10-18 add part number
2024-10-18 Add symbol for Peripheral CAN connector (#35)
    * symbol for Peripheral CAN connector
    * add part number
2024-11-16 added diode protection
2024-11-19 add symbol for PMV35EPE mosfet
2024-11-19 add datasheet
2024-12-17 made lsom symbol and footprint
2025-01-18 added new LDO
2025-01-20 add new dc-dc and ldo
2025-04-13 hi lakshay

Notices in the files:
parts and their libraries:
Copyright 2016 Accelerated Designs. All rights reserved.
